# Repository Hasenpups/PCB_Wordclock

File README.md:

Shield: [![CC BY-NC-SA 4.0][cc-by-nc-sa-shield]][cc-by-nc-sa]

This work is licensed under a
[Creative Commons Attribution-NonCommercial-ShareAlike 4.0 International License][cc-by-nc-sa].

[![CC BY-NC-SA 4.0][cc-by-nc-sa-image]][cc-by-nc-sa]

[cc-by-nc-sa]: http://creativecommons.org/licenses/by-nc-sa/4.0/
[cc-by-nc-sa-image]: https://licensebuttons.net/l/by-nc-sa/4.0/88x31.png
[cc-by-nc-sa-shield]: https://img.shields.io/badge/License-CC%20BY--NC--SA%204.0-lightgrey.svg

## Donations / Spenden
If somebody wants to support me for upcoming projects :)  
- PayPal:  
- Amazon Giftcard: https://www.amazon.de/Amazon-Gutschein-per-E-Mail-Amazon/dp/B0054PDOV8 - stefan.riese@me.com

# PCB_Wordclock

This PCB can be used to build a word clock with WS2812b or SK6812 LEDs. The matrix uses 110 LEDs in a 11x10 grid. The PCB is designed to be used with a front cover of 450x450mm.
There are multiple connections on the board for the LED controller and power supply. 
Additionally there is a data out pin to connect the minute dots after the main LEDs. 

Several mounting holes are also available.

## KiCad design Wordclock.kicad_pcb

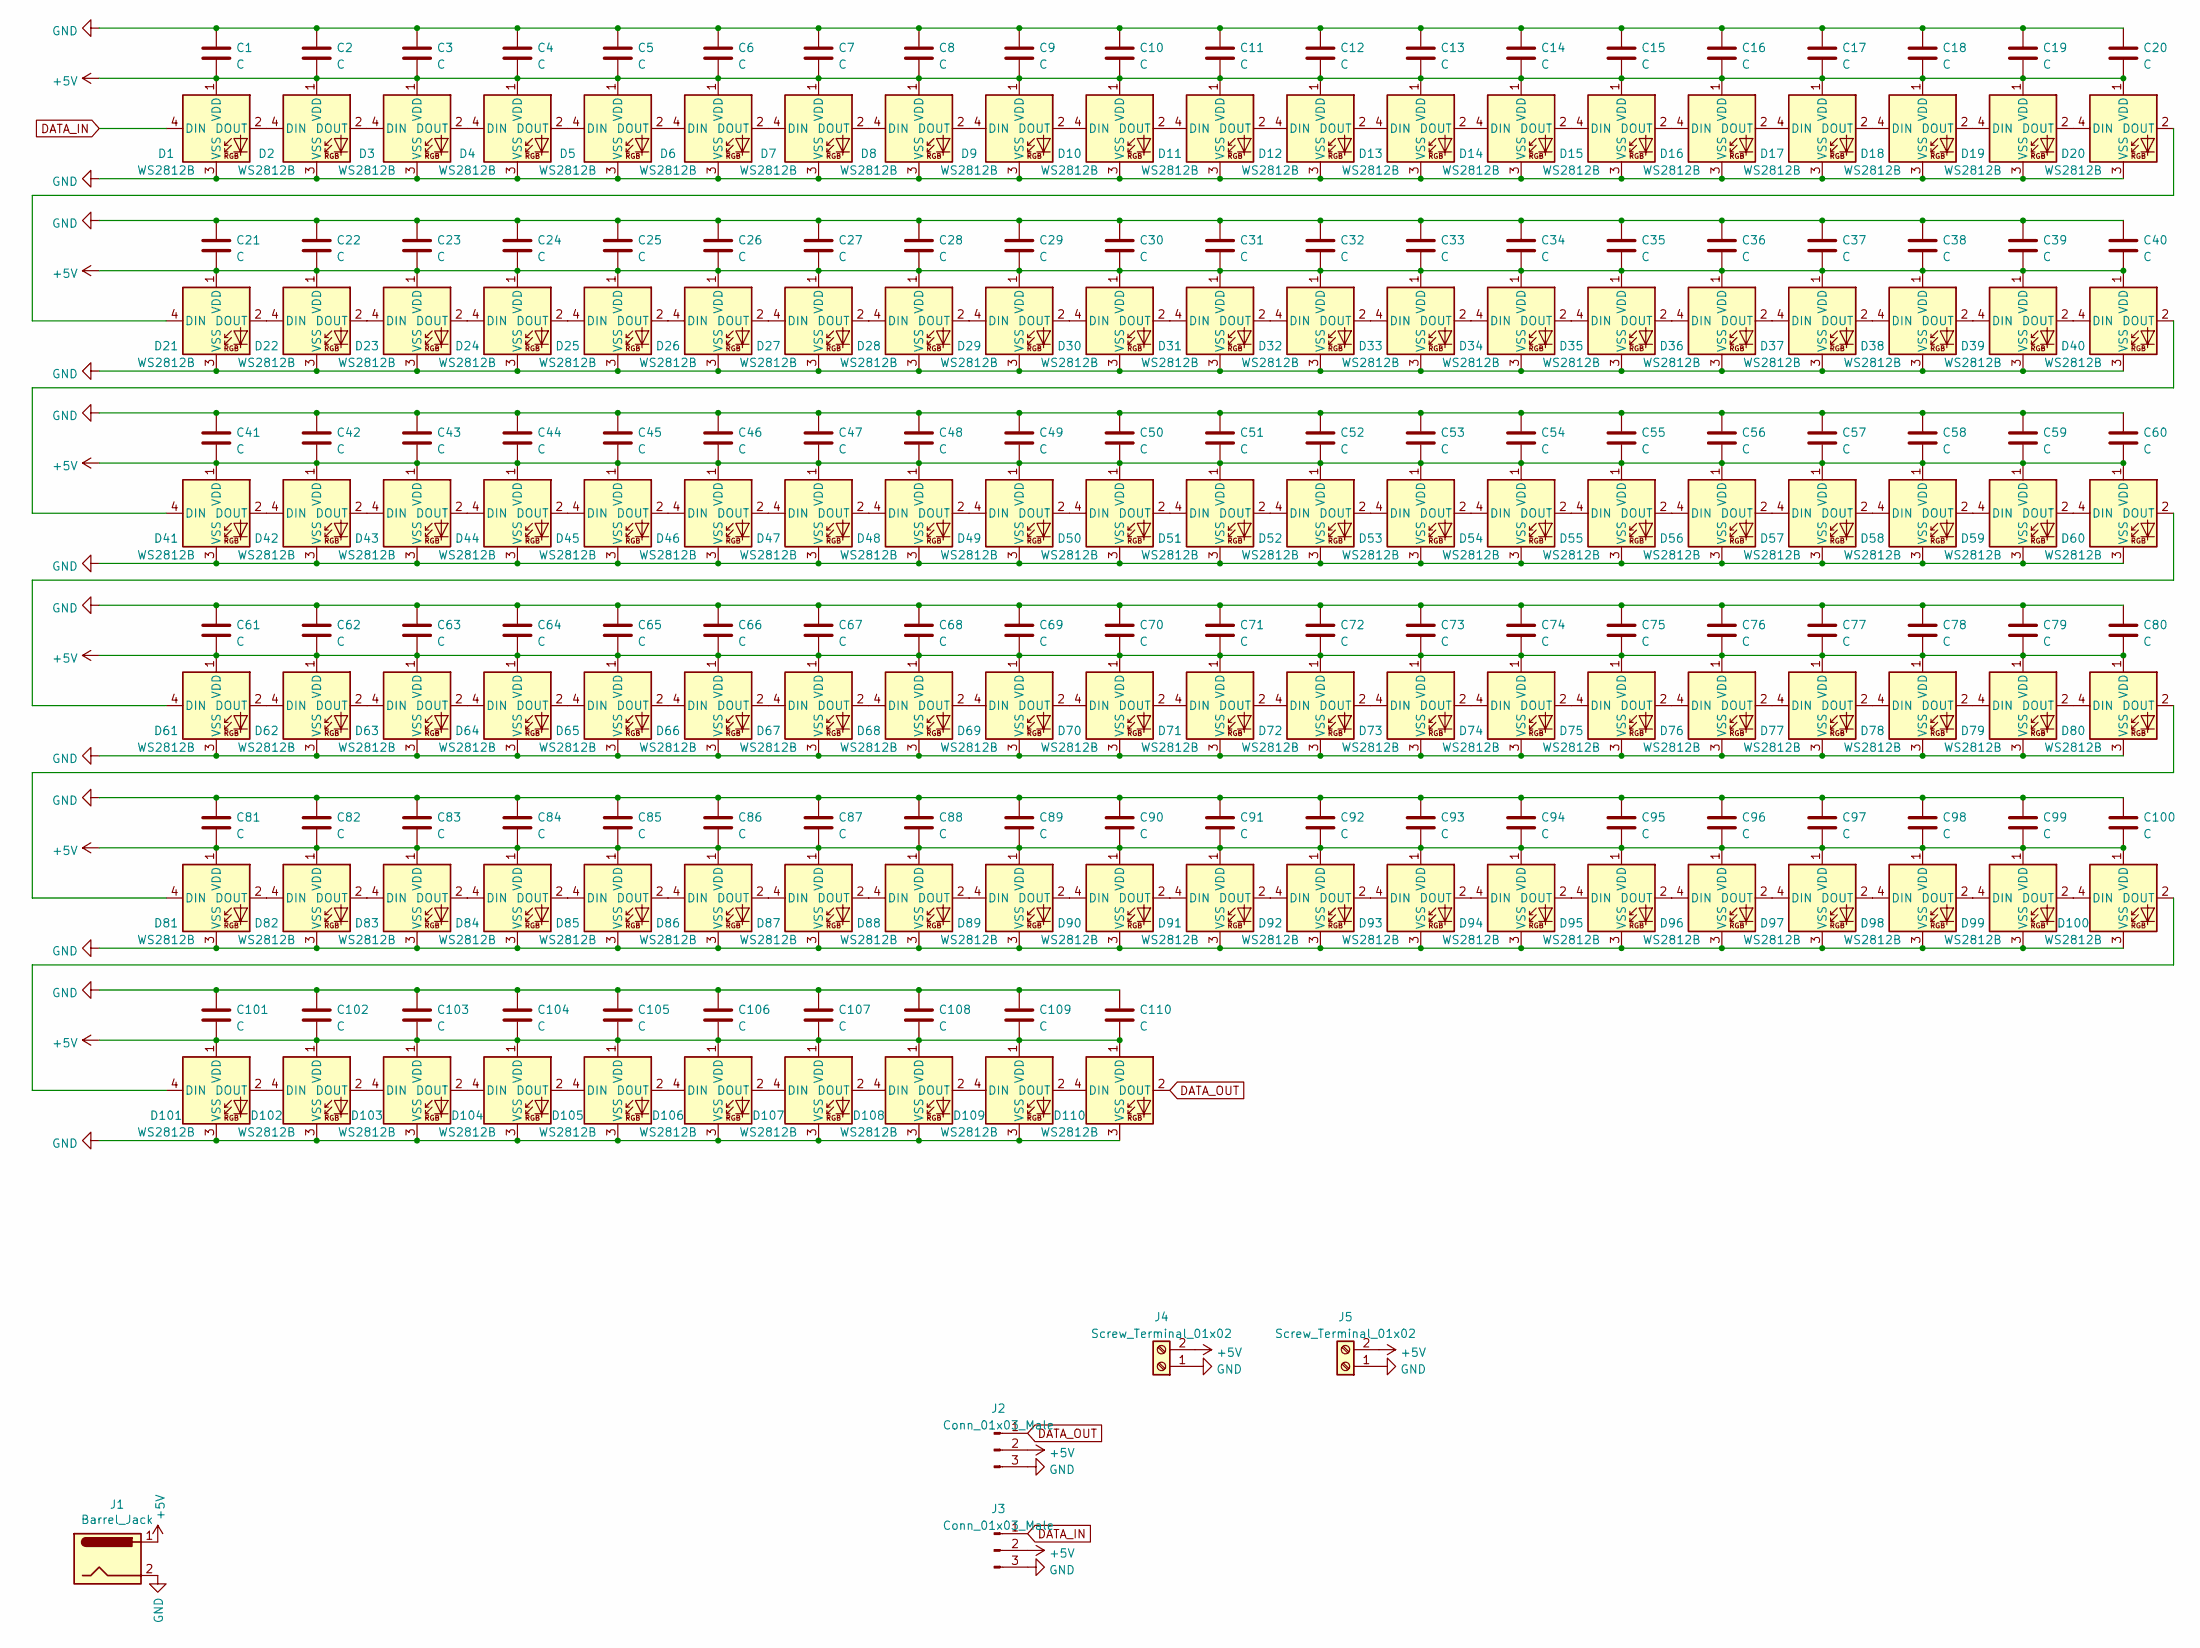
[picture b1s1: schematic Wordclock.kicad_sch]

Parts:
C1, C2, C3, C4, C5, C6, C7, C8, C9, C10, C11, C12, C13, C14, C15, C16, C17, C18, C19, C20, C21, C22, C23, C24, C25, C26, C27, C28, C29, C30, C31, C32, C33, C34, C35, C36, C37, C38, C39, C40, C41, C42, C43, C44, C45, C46, C47, C48, C49, C50, C51, C52, C53, C54, C55, C56, C57, C58, C59, C60, C61, C62, C63, C64, C65, C66, C67, C68, C69, C70, C71, C72, C73, C74, C75, C76, C77, C78, C79, C80, C81, C82, C83, C84, C85, C86, C87, C88, C89, C90, C91, C92, C93, C94, C95, C96, C97, C98, C99, C100, C101, C102, C103, C104, C105, C106, C107, C108, C109, C110: C; C_0805_2012Metric_Pad1.18x1.45mm_HandSolder
D1, D2, D3, D4, D5, D6, D7, D8, D9, D10, D11, D12, D13, D14, D15, D16, D17, D18, D19, D20, D21, D22, D23, D24, D25, D26, D27, D28, D29, D30, D31, D32, D33, D34, D35, D36, D37, D38, D39, D40, D41, D42, D43, D44, D45, D46, D47, D48, D49, D50, D51, D52, D53, D54, D55, D56, D57, D58, D59, D60, D61, D62, D63, D64, D65, D66, D67, D68, D69, D70, D71, D72, D73, D74, D75, D76, D77, D78, D79, D80, D81, D82, D83, D84, D85, D86, D87, D88, D89, D90, D91, D92, D93, D94, D95, D96, D97, D98, D99, D100, D101, D102, D103, D104, D105, D106, D107, D108, D109, D110: WS2812B; LED_WS2812B_PLCC4_5.0x5.0mm_P3.2mm
J1: Barrel_Jack; BarrelJack_Horizontal
J2, J3: Conn_01x03_Male; PinHeader_1x03_P2.54mm_Vertical
J4, J5: Screw_Terminal_01x02; TerminalBlock_bornier-2_P5.08mm

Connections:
+5V: C1.2, C2.2, C3.2, C4.2, C5.2, C6.2, C7.2, C8.2, C9.2, C10.2, C11.2, C12.2, C13.2, C14.2, C15.2, C16.2, C17.2, C18.2, C19.2, C20.2, C21.2, C22.2, C23.2, C24.2, C25.2, C26.2, C27.2, C28.2, C29.2, C30.2, C31.2, C32.2, C33.2, C34.2, C35.2, C36.2, C37.2, C38.2, C39.2, C40.2, C41.2, C42.2, C43.2, C44.2, C45.2, C46.2, C47.2, C48.2, C49.2, C50.2, C51.2, C52.2, C53.2, C54.2, C55.2, C56.2, C57.2, C58.2, C59.2, C60.2, C61.2, C62.2, C63.2, C64.2, C65.2, C66.2, C67.2, C68.2, C69.2, C70.2, C71.2, C72.2, C73.2, C74.2, C75.2, C76.2, C77.2, C78.2, C79.2, C80.2, C81.2, C82.2, C83.2, C84.2, C85.2, C86.2, C87.2, C88.2, C89.2, C90.2, C91.2, C92.2, C93.2, C94.2, C95.2, C96.2, C97.2, C98.2, C99.2, C100.2, C101.2, C102.2, C103.2, C104.2, C105.2, C106.2, C107.2, C108.2, C109.2, C110.2, D1.1 (VDD), D2.1 (VDD), D3.1 (VDD), D4.1 (VDD), D5.1 (VDD), D6.1 (VDD), D7.1 (VDD), D8.1 (VDD), D9.1 (VDD), D10.1 (VDD), D11.1 (VDD), D12.1 (VDD), D13.1 (VDD), D14.1 (VDD), D15.1 (VDD), D16.1 (VDD), D17.1 (VDD), D18.1 (VDD), D19.1 (VDD), D20.1 (VDD), D21.1 (VDD), D22.1 (VDD), D23.1 (VDD), D24.1 (VDD), D25.1 (VDD), D26.1 (VDD), D27.1 (VDD), D28.1 (VDD), D29.1 (VDD), D30.1 (VDD), D31.1 (VDD), D32.1 (VDD), D33.1 (VDD), D34.1 (VDD), D35.1 (VDD), D36.1 (VDD), D37.1 (VDD), D38.1 (VDD), D39.1 (VDD), D40.1 (VDD), D41.1 (VDD), D42.1 (VDD), D43.1 (VDD), D44.1 (VDD), D45.1 (VDD), D46.1 (VDD), D47.1 (VDD), D48.1 (VDD), D49.1 (VDD), D50.1 (VDD), D51.1 (VDD), D52.1 (VDD), D53.1 (VDD), D54.1 (VDD), D55.1 (VDD), D56.1 (VDD), D57.1 (VDD), D58.1 (VDD), D59.1 (VDD), D60.1 (VDD), D61.1 (VDD), D62.1 (VDD), D63.1 (VDD), D64.1 (VDD), D65.1 (VDD), D66.1 (VDD), D67.1 (VDD), D68.1 (VDD), D69.1 (VDD), D70.1 (VDD), D71.1 (VDD), D72.1 (VDD), D73.1 (VDD), D74.1 (VDD), D75.1 (VDD), D76.1 (VDD), D77.1 (VDD), D78.1 (VDD), D79.1 (VDD), D80.1 (VDD), D81.1 (VDD), D82.1 (VDD), D83.1 (VDD), D84.1 (VDD), D85.1 (VDD), D86.1 (VDD), D87.1 (VDD), D88.1 (VDD), D89.1 (VDD), D90.1 (VDD), D91.1 (VDD), D92.1 (VDD), D93.1 (VDD), D94.1 (VDD), D95.1 (VDD), D96.1 (VDD), D97.1 (VDD), D98.1 (VDD), D99.1 (VDD), D100.1 (VDD), D101.1 (VDD), D102.1 (VDD), D103.1 (VDD), D104.1 (VDD), D105.1 (VDD), D106.1 (VDD), D107.1 (VDD), D108.1 (VDD), D109.1 (VDD), D110.1 (VDD), J1.1, J2.2, J3.2, J4.2, J5.2
DATA_IN: D1.4 (DIN), J3.1
DATA_OUT: D110.2 (DOUT), J2.1
GND: C1.1, C2.1, C3.1, C4.1, C5.1, C6.1, C7.1, C8.1, C9.1, C10.1, C11.1, C12.1, C13.1, C14.1, C15.1, C16.1, C17.1, C18.1, C19.1, C20.1, C21.1, C22.1, C23.1, C24.1, C25.1, C26.1, C27.1, C28.1, C29.1, C30.1, C31.1, C32.1, C33.1, C34.1, C35.1, C36.1, C37.1, C38.1, C39.1, C40.1, C41.1, C42.1, C43.1, C44.1, C45.1, C46.1, C47.1, C48.1, C49.1, C50.1, C51.1, C52.1, C53.1, C54.1, C55.1, C56.1, C57.1, C58.1, C59.1, C60.1, C61.1, C62.1, C63.1, C64.1, C65.1, C66.1, C67.1, C68.1, C69.1, C70.1, C71.1, C72.1, C73.1, C74.1, C75.1, C76.1, C77.1, C78.1, C79.1, C80.1, C81.1, C82.1, C83.1, C84.1, C85.1, C86.1, C87.1, C88.1, C89.1, C90.1, C91.1, C92.1, C93.1, C94.1, C95.1, C96.1, C97.1, C98.1, C99.1, C100.1, C101.1, C102.1, C103.1, C104.1, C105.1, C106.1, C107.1, C108.1, C109.1, C110.1, D1.3 (VSS), D2.3 (VSS), D3.3 (VSS), D4.3 (VSS), D5.3 (VSS), D6.3 (VSS), D7.3 (VSS), D8.3 (VSS), D9.3 (VSS), D10.3 (VSS), D11.3 (VSS), D12.3 (VSS), D13.3 (VSS), D14.3 (VSS), D15.3 (VSS), D16.3 (VSS), D17.3 (VSS), D18.3 (VSS), D19.3 (VSS), D20.3 (VSS), D21.3 (VSS), D22.3 (VSS), D23.3 (VSS), D24.3 (VSS), D25.3 (VSS), D26.3 (VSS), D27.3 (VSS), D28.3 (VSS), D29.3 (VSS), D30.3 (VSS), D31.3 (VSS), D32.3 (VSS), D33.3 (VSS), D34.3 (VSS), D35.3 (VSS), D36.3 (VSS), D37.3 (VSS), D38.3 (VSS), D39.3 (VSS), D40.3 (VSS), D41.3 (VSS), D42.3 (VSS), D43.3 (VSS), D44.3 (VSS), D45.3 (VSS), D46.3 (VSS), D47.3 (VSS), D48.3 (VSS), D49.3 (VSS), D50.3 (VSS), D51.3 (VSS), D52.3 (VSS), D53.3 (VSS), D54.3 (VSS), D55.3 (VSS), D56.3 (VSS), D57.3 (VSS), D58.3 (VSS), D59.3 (VSS), D60.3 (VSS), D61.3 (VSS), D62.3 (VSS), D63.3 (VSS), D64.3 (VSS), D65.3 (VSS), D66.3 (VSS), D67.3 (VSS), D68.3 (VSS), D69.3 (VSS), D70.3 (VSS), D71.3 (VSS), D72.3 (VSS), D73.3 (VSS), D74.3 (VSS), D75.3 (VSS), D76.3 (VSS), D77.3 (VSS), D78.3 (VSS), D79.3 (VSS), D80.3 (VSS), D81.3 (VSS), D82.3 (VSS), D83.3 (VSS), D84.3 (VSS), D85.3 (VSS), D86.3 (VSS), D87.3 (VSS), D88.3 (VSS), D89.3 (VSS), D90.3 (VSS), D91.3 (VSS), D92.3 (VSS), D93.3 (VSS), D94.3 (VSS), D95.3 (VSS), D96.3 (VSS), D97.3 (VSS), D98.3 (VSS), D99.3 (VSS), D100.3 (VSS), D101.3 (VSS), D102.3 (VSS), D103.3 (VSS), D104.3 (VSS), D105.3 (VSS), D106.3 (VSS), D107.3 (VSS), D108.3 (VSS), D109.3 (VSS), D110.3 (VSS), J1.2, J2.3, J3.3, J4.1, J5.1
unnamed: D1.2 (DOUT), D2.4 (DIN)
unnamed: D2.2 (DOUT), D3.4 (DIN)
unnamed: D3.2 (DOUT), D4.4 (DIN)
unnamed: D4.2 (DOUT), D5.4 (DIN)
unnamed: D5.2 (DOUT), D6.4 (DIN)
unnamed: D6.2 (DOUT), D7.4 (DIN)
unnamed: D7.2 (DOUT), D8.4 (DIN)
unnamed: D8.2 (DOUT), D9.4 (DIN)
unnamed: D10.2 (DOUT), D11.4 (DIN)
unnamed: D9.2 (DOUT), D10.4 (DIN)
unnamed: D11.2 (DOUT), D12.4 (DIN)
unnamed: D12.2 (DOUT), D13.4 (DIN)
unnamed: D13.2 (DOUT), D14.4 (DIN)
unnamed: D14.2 (DOUT), D15.4 (DIN)
unnamed: D15.2 (DOUT), D16.4 (DIN)
unnamed: D16.2 (DOUT), D17.4 (DIN)
unnamed: D17.2 (DOUT), D18.4 (DIN)
unnamed: D18.2 (DOUT), D19.4 (DIN)
unnamed: D19.2 (DOUT), D20.4 (DIN)
unnamed: D20.2 (DOUT), D21.4 (DIN)
unnamed: D21.2 (DOUT), D22.4 (DIN)
unnamed: D22.2 (DOUT), D23.4 (DIN)
unnamed: D23.2 (DOUT), D24.4 (DIN)
unnamed: D24.2 (DOUT), D25.4 (DIN)
unnamed: D25.2 (DOUT), D26.4 (DIN)
unnamed: D26.2 (DOUT), D27.4 (DIN)
unnamed: D27.2 (DOUT), D28.4 (DIN)
unnamed: D28.2 (DOUT), D29.4 (DIN)
unnamed: D29.2 (DOUT), D30.4 (DIN)
unnamed: D30.2 (DOUT), D31.4 (DIN)
unnamed: D31.2 (DOUT), D32.4 (DIN)
unnamed: D32.2 (DOUT), D33.4 (DIN)
unnamed: D33.2 (DOUT), D34.4 (DIN)
unnamed: D34.2 (DOUT), D35.4 (DIN)
unnamed: D35.2 (DOUT), D36.4 (DIN)
unnamed: D36.2 (DOUT), D37.4 (DIN)
unnamed: D37.2 (DOUT), D38.4 (DIN)
unnamed: D38.2 (DOUT), D39.4 (DIN)
unnamed: D39.2 (DOUT), D40.4 (DIN)
unnamed: D40.2 (DOUT), D41.4 (DIN)
unnamed: D41.2 (DOUT), D42.4 (DIN)
unnamed: D42.2 (DOUT), D43.4 (DIN)
unnamed: D43.2 (DOUT), D44.4 (DIN)
unnamed: D44.2 (DOUT), D45.4 (DIN)
unnamed: D45.2 (DOUT), D46.4 (DIN)
unnamed: D46.2 (DOUT), D47.4 (DIN)
unnamed: D47.2 (DOUT), D48.4 (DIN)
unnamed: D48.2 (DOUT), D49.4 (DIN)
unnamed: D49.2 (DOUT), D50.4 (DIN)
unnamed: D50.2 (DOUT), D51.4 (DIN)
unnamed: D51.2 (DOUT), D52.4 (DIN)
unnamed: D52.2 (DOUT), D53.4 (DIN)
unnamed: D53.2 (DOUT), D54.4 (DIN)
unnamed: D54.2 (DOUT), D55.4 (DIN)
unnamed: D55.2 (DOUT), D56.4 (DIN)
unnamed: D56.2 (DOUT), D57.4 (DIN)
unnamed: D57.2 (DOUT), D58.4 (DIN)
unnamed: D58.2 (DOUT), D59.4 (DIN)
unnamed: D59.2 (DOUT), D60.4 (DIN)
unnamed: D60.2 (DOUT), D61.4 (DIN)
unnamed: D61.2 (DOUT), D62.4 (DIN)
unnamed: D62.2 (DOUT), D63.4 (DIN)
unnamed: D63.2 (DOUT), D64.4 (DIN)
unnamed: D64.2 (DOUT), D65.4 (DIN)
unnamed: D65.2 (DOUT), D66.4 (DIN)
unnamed: D66.2 (DOUT), D67.4 (DIN)
unnamed: D67.2 (DOUT), D68.4 (DIN)
unnamed: D68.2 (DOUT), D69.4 (DIN)
unnamed: D69.2 (DOUT), D70.4 (DIN)
unnamed: D70.2 (DOUT), D71.4 (DIN)
unnamed: D71.2 (DOUT), D72.4 (DIN)
unnamed: D72.2 (DOUT), D73.4 (DIN)
unnamed: D73.2 (DOUT), D74.4 (DIN)
unnamed: D74.2 (DOUT), D75.4 (DIN)
unnamed: D75.2 (DOUT), D76.4 (DIN)
unnamed: D76.2 (DOUT), D77.4 (DIN)
unnamed: D77.2 (DOUT), D78.4 (DIN)
unnamed: D78.2 (DOUT), D79.4 (DIN)
unnamed: D79.2 (DOUT), D80.4 (DIN)
unnamed: D80.2 (DOUT), D81.4 (DIN)
unnamed: D81.2 (DOUT), D82.4 (DIN)
unnamed: D82.2 (DOUT), D83.4 (DIN)
unnamed: D83.2 (DOUT), D84.4 (DIN)
unnamed: D84.2 (DOUT), D85.4 (DIN)
unnamed: D85.2 (DOUT), D86.4 (DIN)
unnamed: D86.2 (DOUT), D87.4 (DIN)
unnamed: D87.2 (DOUT), D88.4 (DIN)
unnamed: D88.2 (DOUT), D89.4 (DIN)
unnamed: D89.2 (DOUT), D90.4 (DIN)
unnamed: D90.2 (DOUT), D91.4 (DIN)
unnamed: D91.2 (DOUT), D92.4 (DIN)
unnamed: D92.2 (DOUT), D93.4 (DIN)
unnamed: D93.2 (DOUT), D94.4 (DIN)
unnamed: D94.2 (DOUT), D95.4 (DIN)
unnamed: D95.2 (DOUT), D96.4 (DIN)
unnamed: D96.2 (DOUT), D97.4 (DIN)
unnamed: D97.2 (DOUT), D98.4 (DIN)
unnamed: D98.2 (DOUT), D99.4 (DIN)
unnamed: D100.2 (DOUT), D101.4 (DIN)
unnamed: D99.2 (DOUT), D100.4 (DIN)
unnamed: D101.2 (DOUT), D102.4 (DIN)
unnamed: D102.2 (DOUT), D103.4 (DIN)
unnamed: D103.2 (DOUT), D104.4 (DIN)
unnamed: D104.2 (DOUT), D105.4 (DIN)
unnamed: D105.2 (DOUT), D106.4 (DIN)
unnamed: D106.2 (DOUT), D107.4 (DIN)
unnamed: D107.2 (DOUT), D108.4 (DIN)
unnamed: D108.2 (DOUT), D109.4 (DIN)
unnamed: D109.2 (DOUT), D110.4 (DIN)

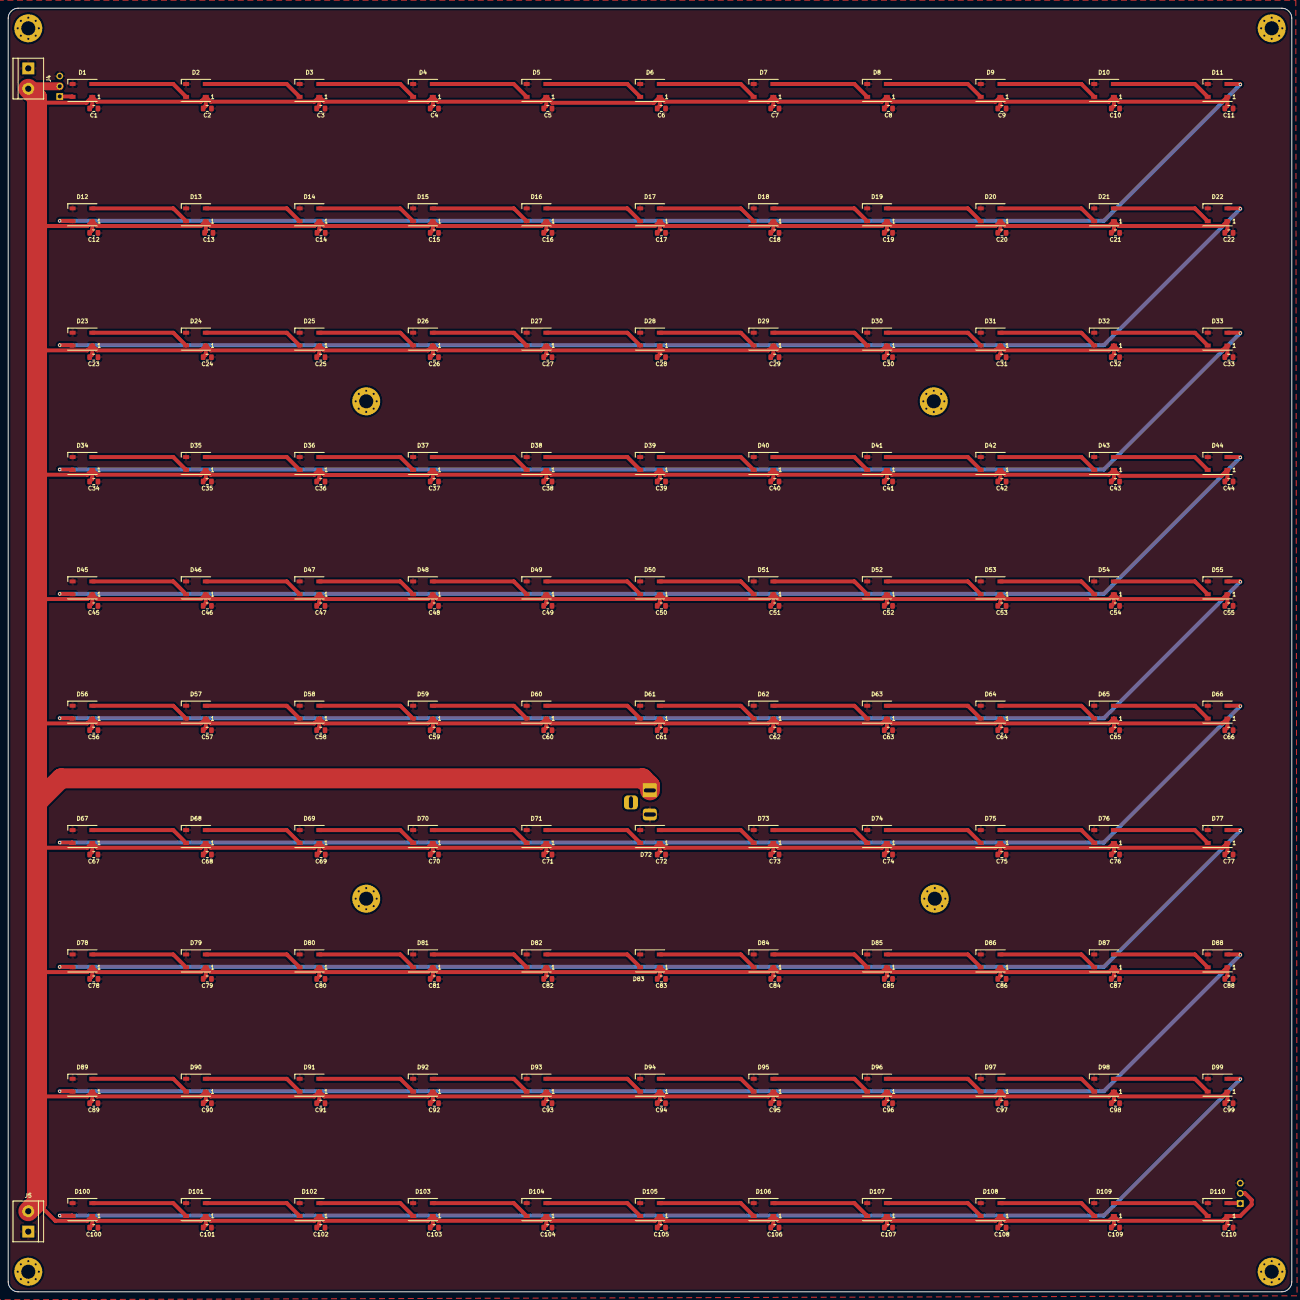
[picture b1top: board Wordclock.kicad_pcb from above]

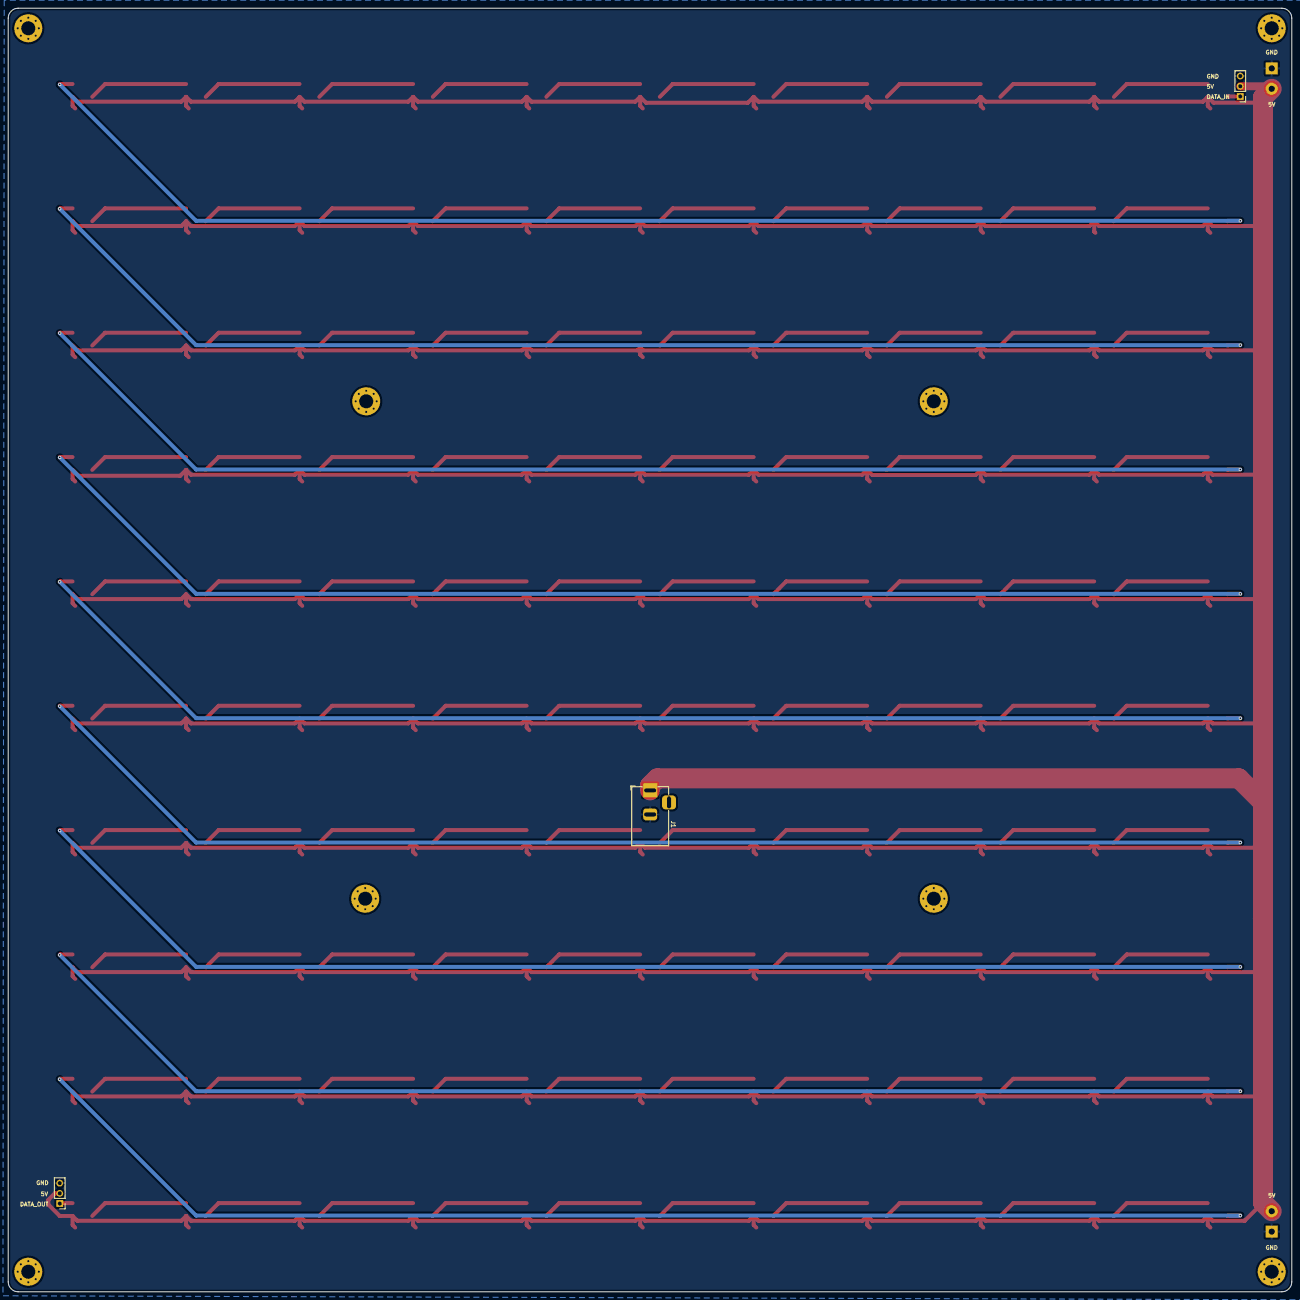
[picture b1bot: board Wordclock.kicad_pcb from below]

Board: 2 copper layers, 320.0 x 320.0 mm, 233 parts (3 on the bottom side), 113 nets.

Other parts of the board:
Hole1, Hole2, Hole3, Hole4, Hole5, Hole6, Hole7, Hole8: MountingHole_3.5mm_Pad_Via

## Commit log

2022-03-14 - initial commit
2022-03-15 - first final version
2022-03-15 - update Gerber.rar
2022-03-31 - fix print on silkscreen
